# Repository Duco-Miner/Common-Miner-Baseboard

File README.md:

# Common-Miner-Baseboard

The Common Miner Baseboard forms the backbone of the DUCO Miner Rack which holds the [AVR-Miners](https://github.com/Duco-Miner/AVR-Miner) & the [ESP32-Miner](https://github.com/Duco-Miner/ESP32-Miner) together. The Miner Basebaord ensures proper connectivity between the devices & is also responsible for providing consistent power supply to every board on it. The Common Miner Baseboard can be stacked on top of one another to create a pile of multiple Baseboards & Expansion Boards.

These are the KiCAD Project files for the Common-Miner-Baseboard PCB.

Please feel free to modify the design files as per your requirements. Improvements are always appreciated !!!

---
### Preview:

1) PCB View 1:

2) PCB View 2:

3) PCB Front View:

4) PCB Back View:

---

### PCB Specifications:

- Layers: 2
- Size: 108mm x 38mm

---

### Components:

| Sr. No. | Component                               | Package | Quantity |                Marking on PCB                |
| :-----: | :-------------------------------------- | :-----: | :------: | :------------------------------------------: |
|    6    | 1k Resistor                             |  0805   |    11    | R1, R2, R3, R4, R5, R6, R7, R8, R9, R10, R11 |
|    7    | 0R Resistor                             |  0805   |    2     |                   R12, R13                   |
|    5    | 4.7k Resistor                           |  0805   |    2     |                   R14, R15                   |
|    9    | 1x5 2.54mm Pin Socket Female - Vertical |    -    |    11    | J1, J2, J3, J4, J5, J6, J7, J8, J9, J10, J11 |
|   10    | 1x4 5.08mm Screw Terminal Block         |    -    |    1     |                     J12                      |
|   14    | LED (Blue Color)                        |  0805   |    11    | D1, D2, D3, D4, D5, D6, D7, D8, D9, D10, D11 |

---

### Additional Links:

- Check out the awesome Duino Coin Project at: [https://duinocoin.com](https://duinocoin.com)
- Duino Coin Wallet: [https://wallet.duinocoin.com](https://wallet.duinocoin.com)

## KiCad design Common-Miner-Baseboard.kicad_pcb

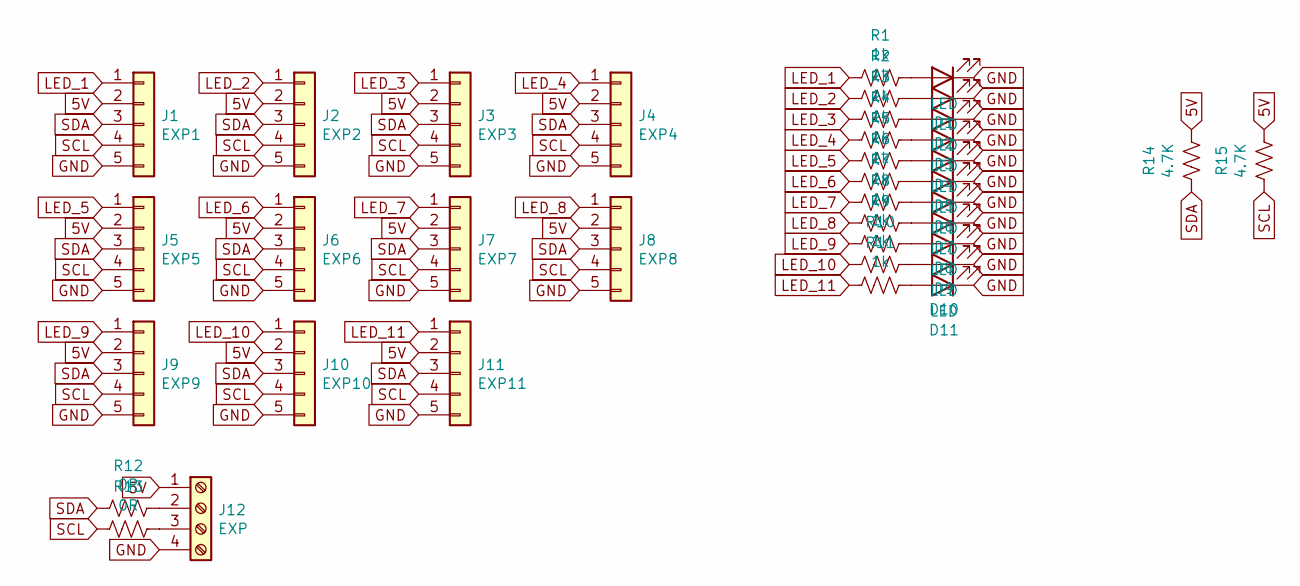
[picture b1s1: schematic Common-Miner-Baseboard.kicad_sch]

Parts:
D1, D2, D3, D4, D5, D6, D7, D8, D9, D10, D11: LED; LED_0805_2012Metric
J1: EXP1; PinSocket_1x05_P2.54mm_Vertical
J2: EXP2; PinSocket_1x05_P2.54mm_Vertical
J3: EXP3; PinSocket_1x05_P2.54mm_Vertical
J4: EXP4; PinSocket_1x05_P2.54mm_Vertical
J5: EXP5; PinSocket_1x05_P2.54mm_Vertical
J6: EXP6; PinSocket_1x05_P2.54mm_Vertical
J7: EXP7; PinSocket_1x05_P2.54mm_Vertical
J8: EXP8; PinSocket_1x05_P2.54mm_Vertical
J9: EXP9; PinSocket_1x05_P2.54mm_Vertical
J10: EXP10; PinSocket_1x05_P2.54mm_Vertical
J11: EXP11; PinSocket_1x05_P2.54mm_Vertical
J12: EXP; TerminalBlock_bornier-4_P5.08mm
R1, R2, R3, R4, R5, R6, R7, R8, R9, R10, R11: 1k; R_0805_2012Metric
R12, R13: 0R; R_0805_2012Metric
R14, R15: 4.7K; R_0805_2012Metric

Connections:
5V: J1.2, J2.2, J3.2, J4.2, J5.2, J6.2, J7.2, J8.2, J9.2, J10.2, J11.2, J12.1, R14.1, R15.1
GND: D1.1 (K), D2.1 (K), D3.1 (K), D4.1 (K), D5.1 (K), D6.1 (K), D7.1 (K), D8.1 (K), D9.1 (K), D10.1 (K), D11.1 (K), J1.5, J2.5, J3.5, J4.5, J5.5, J6.5, J7.5, J8.5, J9.5, J10.5, J11.5, J12.4
LED_1: J1.1, R1.2
LED_2: J2.1, R2.2
LED_3: J3.1, R3.2
LED_4: J4.1, R4.2
LED_5: J5.1, R5.2
LED_6: J6.1, R6.2
LED_7: J7.1, R7.2
LED_8: J8.1, R8.2
LED_9: J9.1, R9.2
LED_10: J10.1, R10.2
LED_11: J11.1, R11.2
unnamed: D1.2 (A), R1.1
unnamed: D2.2 (A), R2.1
unnamed: D3.2 (A), R3.1
unnamed: D4.2 (A), R4.1
unnamed: D5.2 (A), R5.1
unnamed: D6.2 (A), R6.1
unnamed: D7.2 (A), R7.1
unnamed: D8.2 (A), R8.1
unnamed: D9.2 (A), R9.1
unnamed: D10.2 (A), R10.1
unnamed: D11.2 (A), R11.1
unnamed: J12.2, R12.1
unnamed: J12.3, R13.1
SCL: J1.4, J2.4, J3.4, J4.4, J5.4, J6.4, J7.4, J8.4, J9.4, J10.4, J11.4, R13.2, R15.2
SDA: J1.3, J2.3, J3.3, J4.3, J5.3, J6.3, J7.3, J8.3, J9.3, J10.3, J11.3, R12.2, R14.2

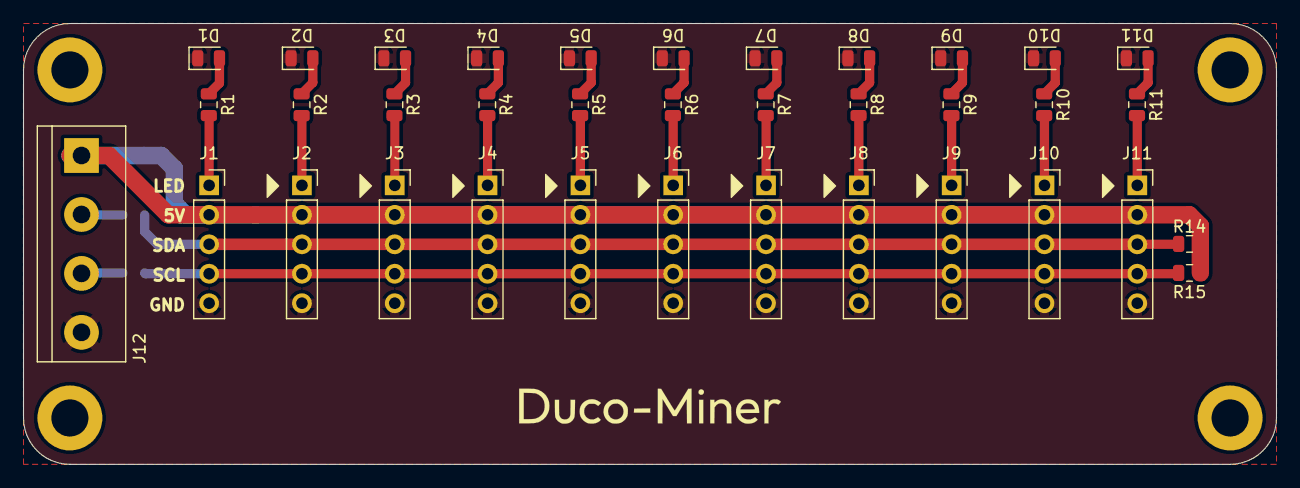
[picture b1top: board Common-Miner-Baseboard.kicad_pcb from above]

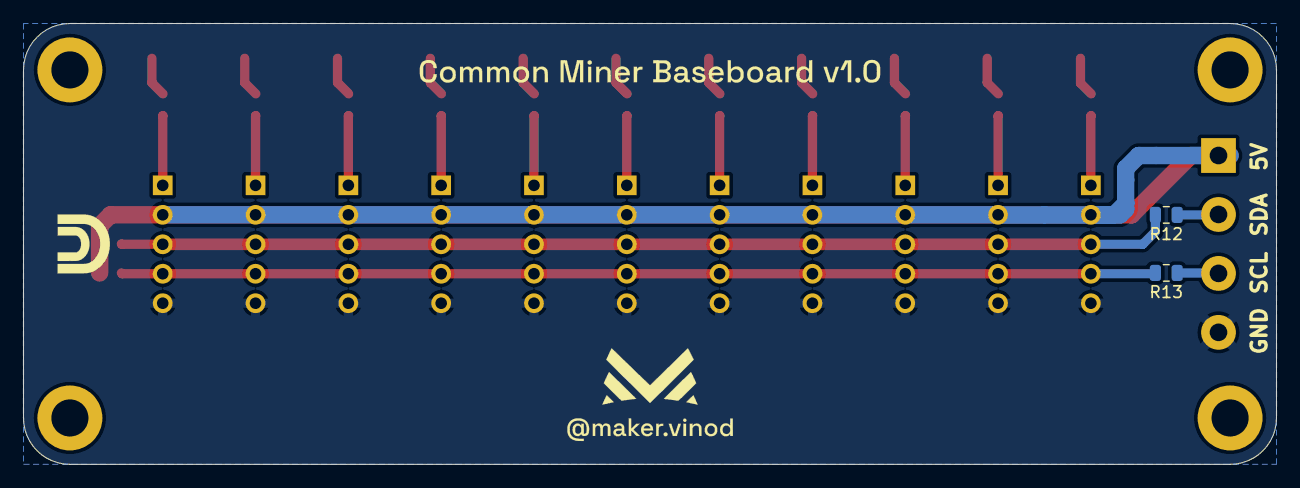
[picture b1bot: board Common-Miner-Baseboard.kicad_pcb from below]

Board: 2 copper layers, 108.0 x 38.0 mm, 38 parts (2 on the bottom side), 28 nets.

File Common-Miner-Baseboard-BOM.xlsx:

|  |  | Common-Miner-Baseboard BOM (Bill of Materials)
Item # | *Designator | *Qty | Manufacturer | *Mfg Part # | Description / Value | *Package/Footprint | Type | Your Instructions / Notes
1 | D1, D2, D3, D4, D5, D6, D7, D8, D9, D10, D11 | 11 | Lite-On Inc. | LTST-C171TBKT | LED Blue | 0805 | SMD
2 | J1,J2,J3,J4,J5,J6,J7,J8,J9,J10,J11 | 11 | Adam Tech | RECEPTACLE STRIP 5P 2.54MM PITCH | 2.54mm Pin Header Female 1x05 | PinHeader_1x05_P2.54mm_Vertical | PTH
13 | J12 | 1 | Adam Tech | EB147A-04-D | Screw Terminal P5.08mm 1x4 | Screw Terminal P5.08mm 1x4 | PTH
14 | R1, R2, R3, R4, R5, R6, R7, R8, R9, R10, R11 | 11 | Stackpole Electronics Inc | RMCF0805FT1K00 | 1k | 0805 | SMD
15 | R12, R13 | 2 | Bourns Inc. | CR0805AJ/-000EAS | 0R | 0805 | SMD
16 | R14, R15 | 2 | YAGEO | RC0805FR-074K7L | 4.7k | 0805 | SMD
 |  |  |  |  |  |  |  |  |  |  |  |  |  |  |  |  | ESP32-MINER-BOM

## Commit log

2022-05-25 Updated README & added Images
2023-11-18 Updated project for KiCad 7 & added Gerber Files
